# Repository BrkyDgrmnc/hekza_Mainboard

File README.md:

# hekza_Mainboard
Teknofest 2021 hekzakopter mainboard.

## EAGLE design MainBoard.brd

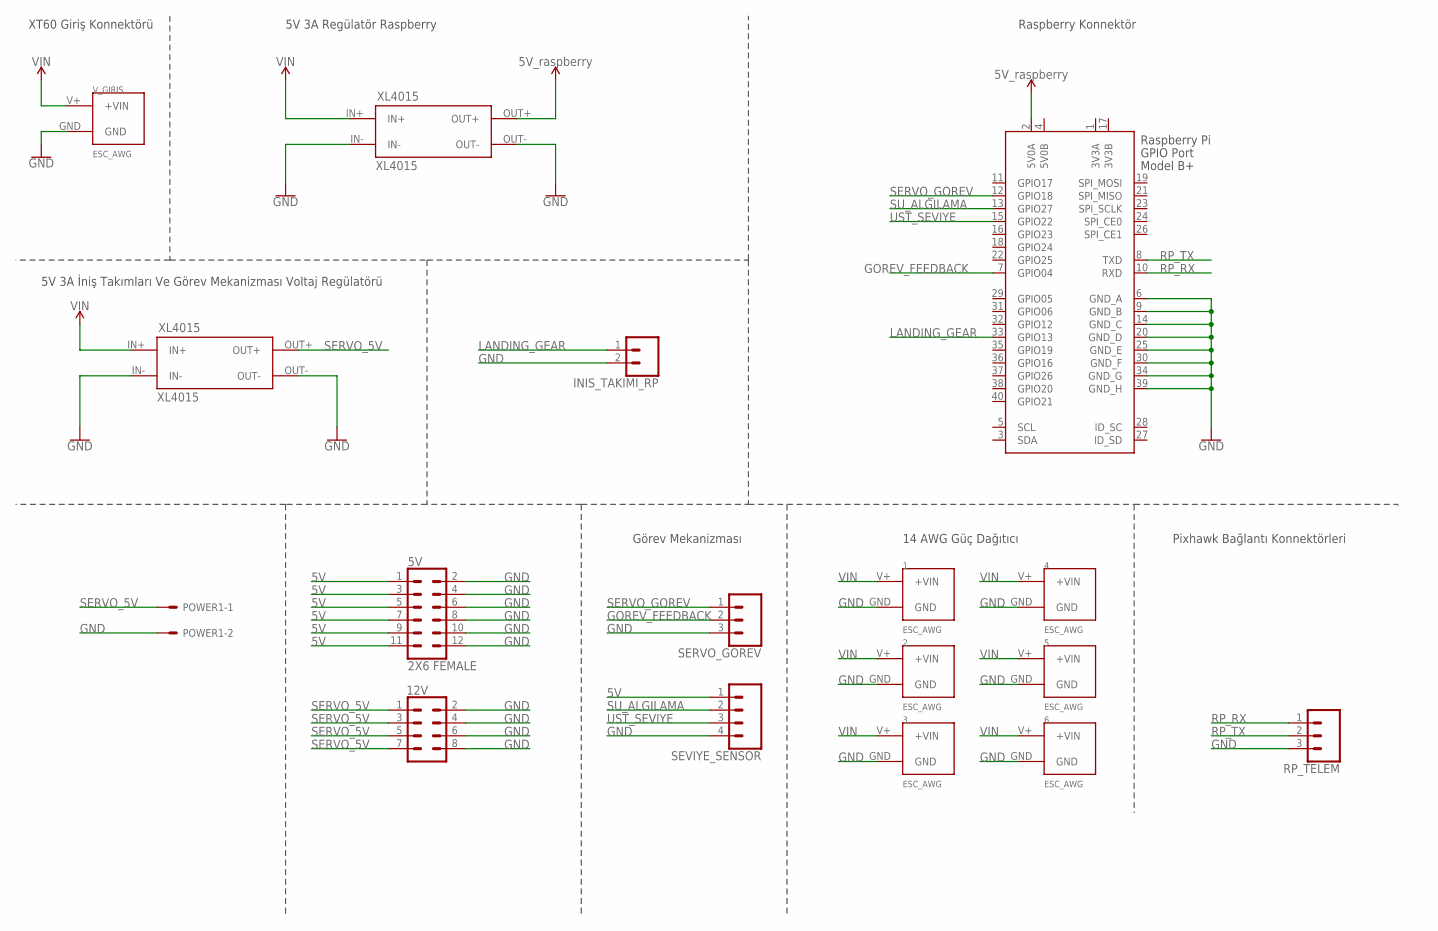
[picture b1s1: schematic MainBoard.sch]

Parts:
1, 2, 3, 4, 5, 6: ESC_AWG
5V: 2X6 FEMALE; 2X6
12V: CONN_04X2; 2X4
INIS_TAKIMI_RP: CONN_02; 1X02
POWER1: 22-27-2021-02; 6410-02
RP_TELEM: CONN_03; 1X03
SERVO_GOREV: CONN_03; 1X03
SEVIYE_SENSOR: CONN_04; 1X04
U$3, U$4: XL4015
V_GIRIS: ESC_AWG
X1: RASPI_BOARD_B+#_E4; RASPI_BOARD_B+_EDGES_4DRILL

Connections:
3V3A: X1.1 (3V3A)
3V3B: X1.17 (3V3B)
5V: 5V.1, 5V.3, 5V.5, 5V.7, 5V.9, 5V.11, SEVIYE_SENSOR.1, U$3.OUT+, X1.2 (5V0A)
5V0B: X1.4 (5V0B)
GND: 1.GND, 2.GND, 3.GND, 4.GND, 5.GND, 5V.2, 5V.4, 5V.6, 5V.8, 5V.10, 5V.12, 6.GND, 12V.2, 12V.4, 12V.6, 12V.8, INIS_TAKIMI_RP.2, POWER1.2, RP_TELEM.3, SERVO_GOREV.3, SEVIYE_SENSOR.4, U$3.IN-, U$3.OUT-, U$4.IN-, U$4.OUT-, V_GIRIS.GND, X1.6 (GND_A), X1.9 (GND_B), X1.14 (GND_C), X1.20 (GND_D), X1.25 (GND_E), X1.30 (GND_F), X1.34 (GND_G), X1.39 (GND_H)
GOREV_FEEDBACK: SERVO_GOREV.2, X1.7 (GPIO04)
LANDING_GEAR: INIS_TAKIMI_RP.1, X1.33 (GPIO13)
RP_RX: RP_TELEM.1, X1.10 (RXD)
RP_TX: RP_TELEM.2, X1.8 (TXD)
SERVO_5V: 12V.1, 12V.3, 12V.5, 12V.7, POWER1.1, U$4.OUT+
SERVO_GOREV: SERVO_GOREV.1, X1.12 (GPIO18)
SU_ALGILAMA: SEVIYE_SENSOR.2, X1.13 (GPIO27)
UST_SEVIYE: SEVIYE_SENSOR.3, X1.15 (GPIO22)
VIN: 1.V+ (+VIN), 2.V+ (+VIN), 3.V+ (+VIN), 4.V+ (+VIN), 5.V+ (+VIN), 6.V+ (+VIN), U$3.IN+, U$4.IN+, V_GIRIS.V+ (+VIN)

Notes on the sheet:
5V 3A Regülatör Raspberry
Pixhawk Bağlantı Konnektörleri
5V 3A İniş Takımları Ve Görev Mekanizması Voltaj Regülatörü
Görev Mekanizması
14 AWG Güç Dağıtıcı
Raspberry Konnektör
XT60 Giriş Konnektörü

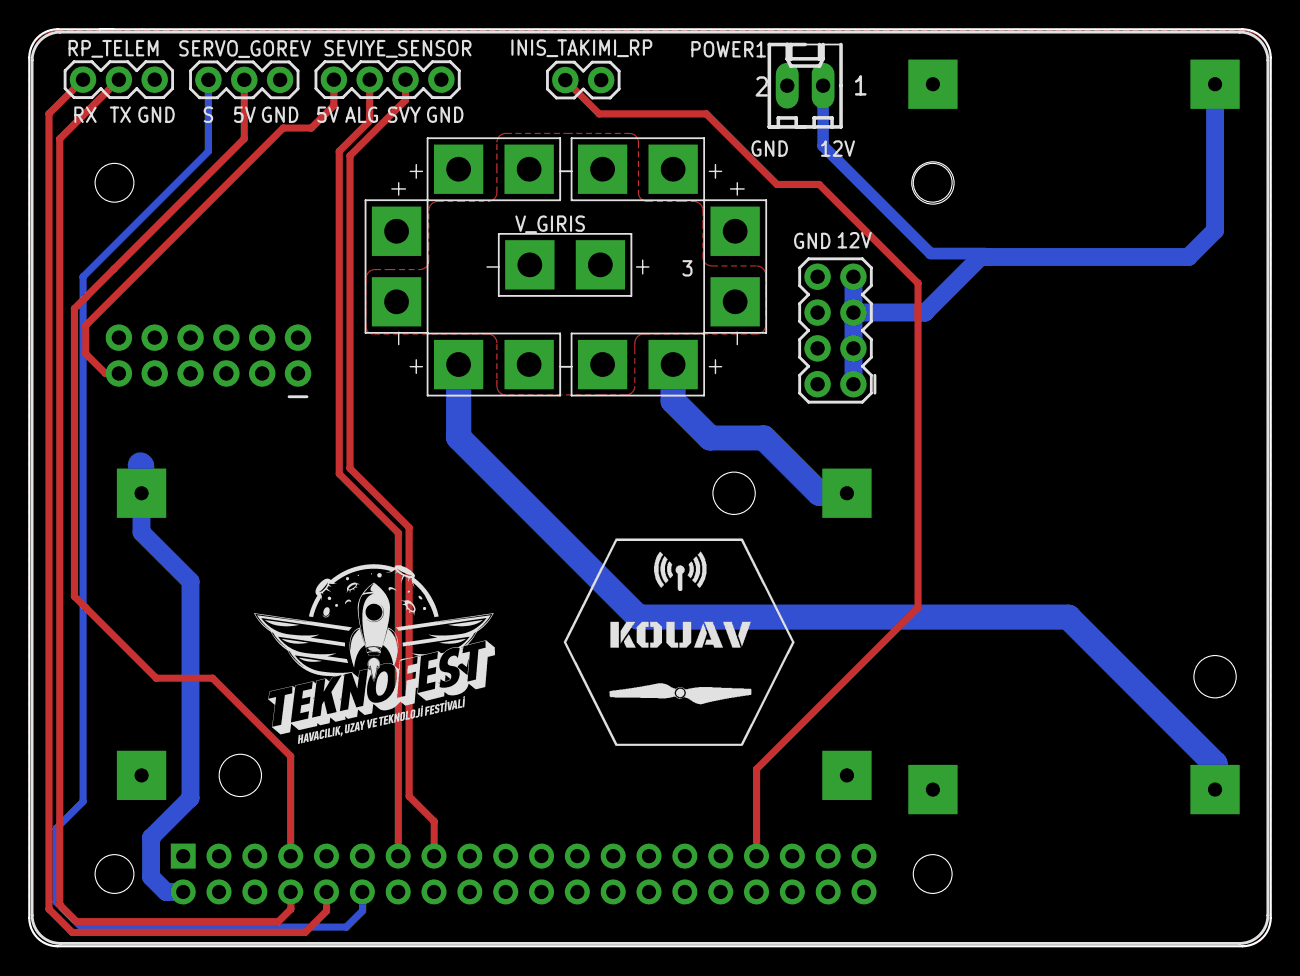
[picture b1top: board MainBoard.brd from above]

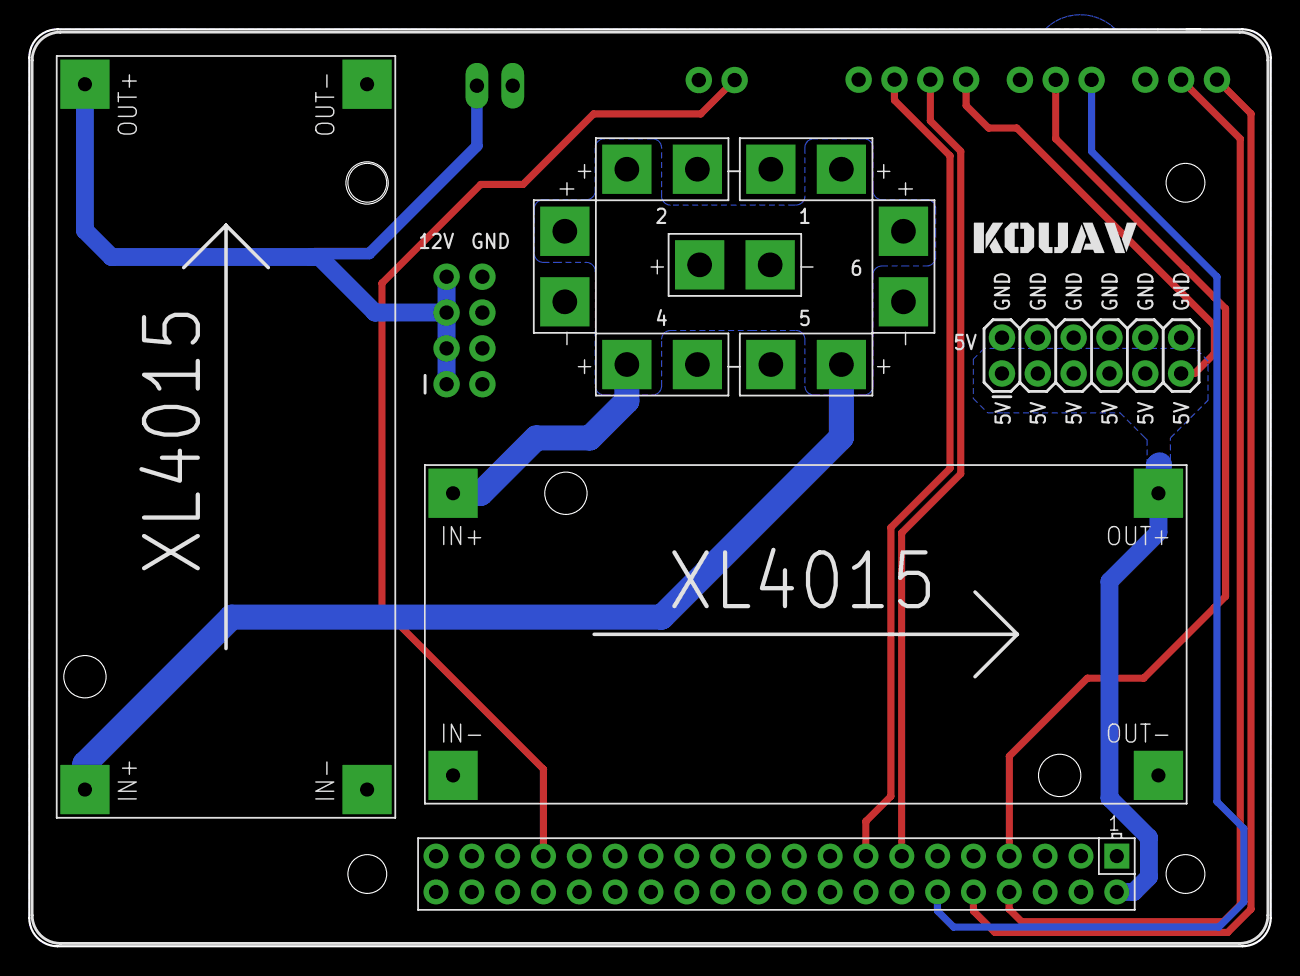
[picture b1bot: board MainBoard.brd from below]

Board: 2 copper layers, 88.0 x 65.0 mm, 20 parts (6 on the bottom side), 11 nets.

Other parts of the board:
U$1: KOUAV_LOGO
U$2: TEKNOFEST_LOGO
U$6: KOUAV_YAZI

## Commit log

2022-01-31 Create EAGLE

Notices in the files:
parts and their libraries:
SparkFun-Connectors: Licensing: Creative Commons ShareAlike 4.0 International - https://creativecommons.org/licenses/by-sa/4.0
